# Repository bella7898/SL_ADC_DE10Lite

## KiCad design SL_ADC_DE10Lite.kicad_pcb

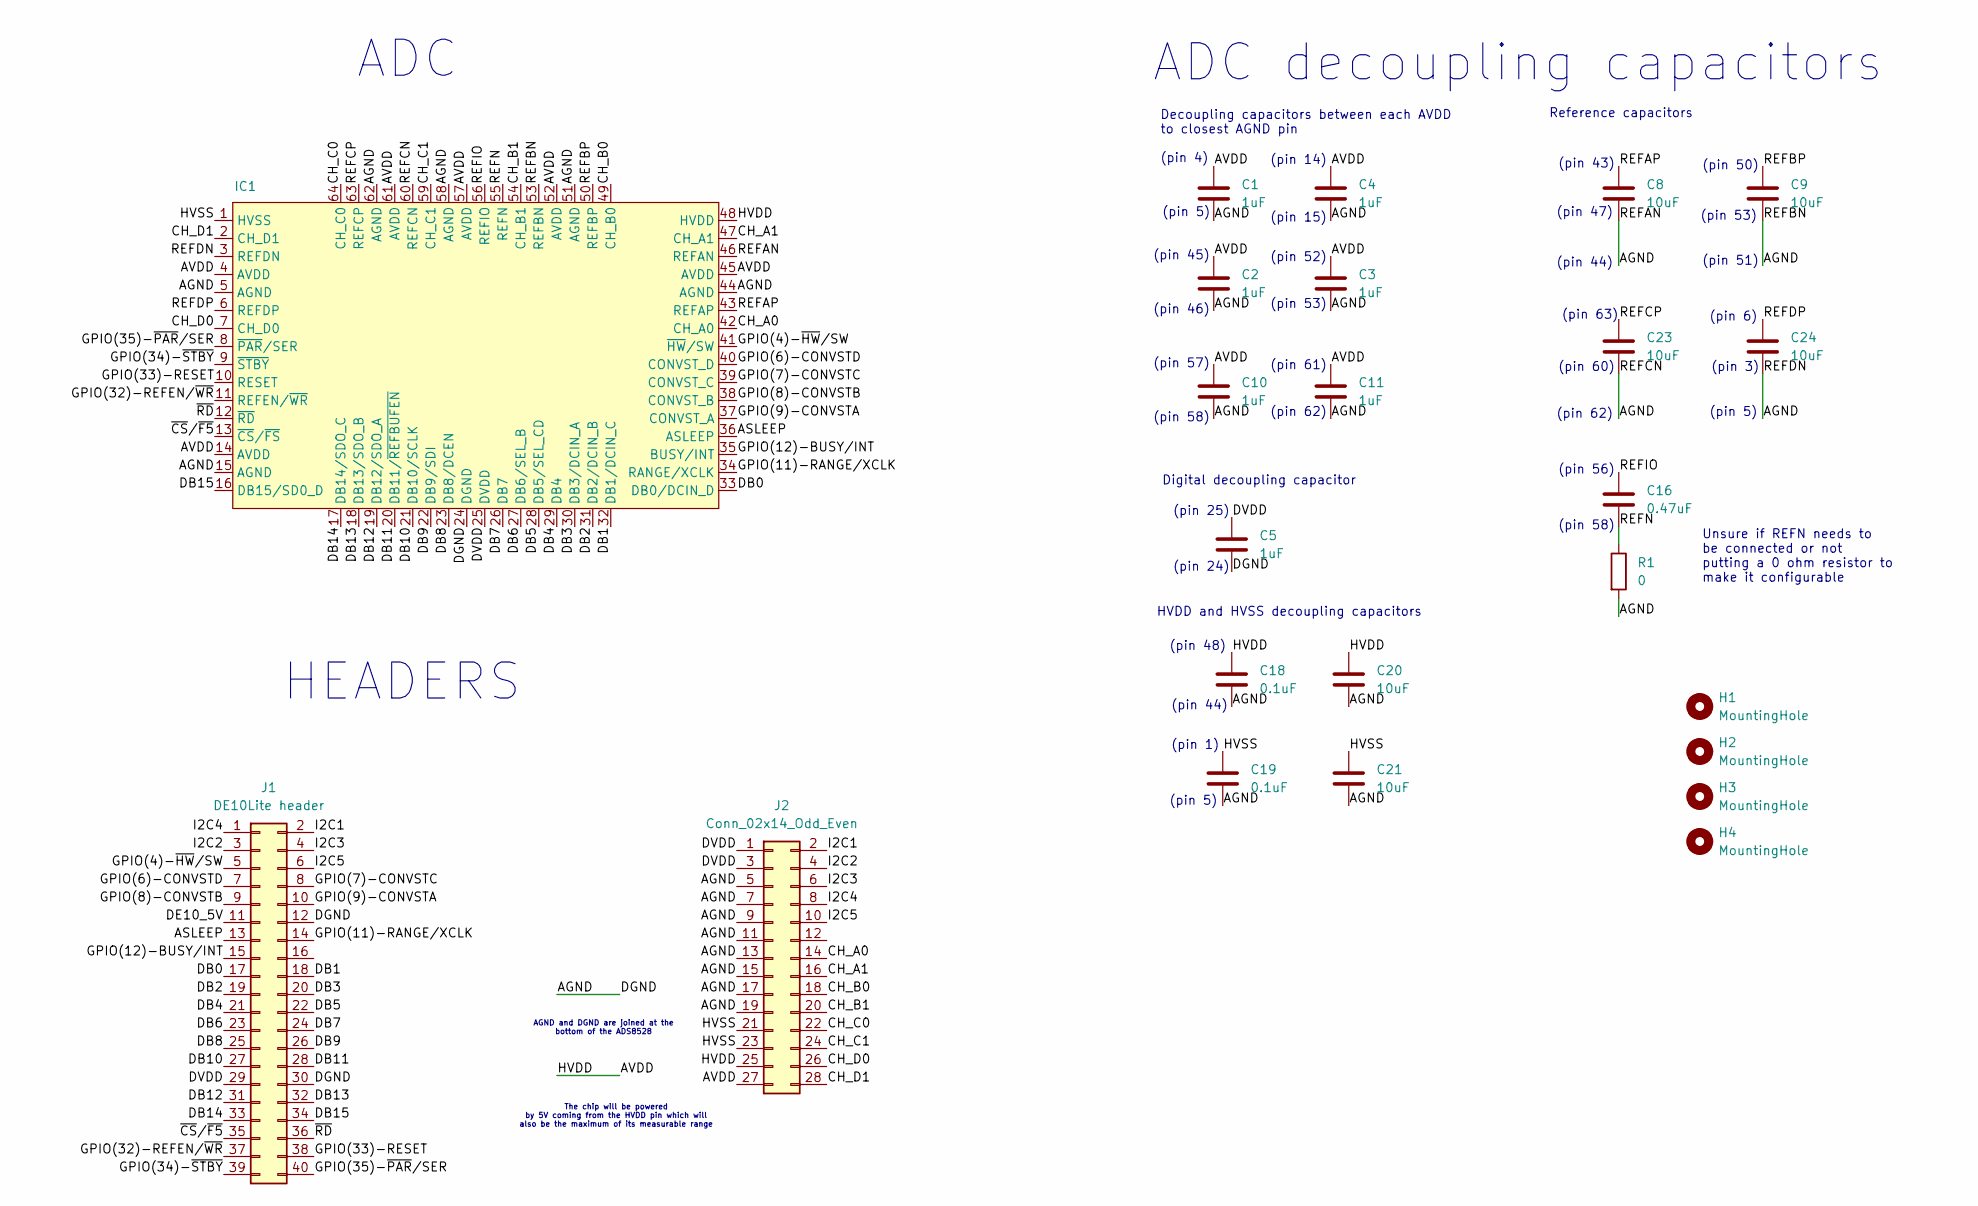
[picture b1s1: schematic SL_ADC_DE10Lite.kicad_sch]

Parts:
C1, C2, C3, C4, C5, C10, C11: 1uF; C_0805_2012Metric_Pad1.18x1.45mm_HandSolder; Manufacturer_Part_Number CL21B105KBFNNNE
C8, C9, C20, C21, C23, C24: 10uF; C_0805_2012Metric_Pad1.18x1.45mm_HandSolder; Manufacturer_Part_Number CL21B106KOQNNNE
C16: 0.47uF; C_0805_2012Metric_Pad1.18x1.45mm_HandSolder; Manufacturer_Part_Number CL21B106KOQNNNE
C18, C19: 0.1uF; C_0805_2012Metric_Pad1.18x1.45mm_HandSolder; Manufacturer_Part_Number CL21B106KOQNNNE
H1, H2, H3, H4: MountingHole; MountingHole_2.5mm
IC1: TQFP-64_10x10mm_P0.5mm
J1: DE10Lite header; PinHeader_2x20_P2.54mm_Vertical
J2: Conn_02x14_Odd_Even; PinHeader_2x14_P2.54mm_Vertical
R1: 0; LED_0805_2012Metric

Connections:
/AGND: C1.2, C2.2, C3.2, C4.2, C5.2, C8.2, C9.2, C10.2, C11.2, C18.2, C19.2, C20.2, C21.2, C23.2, C24.2, IC1.3 (REFDN), IC1.5 (AGND), IC1.15 (AGND), IC1.24 (DGND), IC1.44 (AGND), IC1.46 (REFAN), IC1.51 (AGND), IC1.53 (REFBN), IC1.58 (AGND), IC1.60 (REFCN), IC1.62 (AGND), J1.12, J1.30, J2.5, J2.7, J2.9, J2.11, J2.13, J2.15, J2.17, J2.19, R1.2
/ASLEEP: IC1.36 (ASLEEP), J1.13
/AVDD: C1.1, C2.1, C3.1, C4.1, C10.1, C11.1, C18.1, C20.1, IC1.4 (AVDD), IC1.14 (AVDD), IC1.45 (AVDD), IC1.48 (HVDD), IC1.52 (AVDD), IC1.57 (AVDD), IC1.61 (AVDD), J2.25, J2.27
/CH_A0: IC1.42 (CH_A0), J2.14
/CH_A1: IC1.47 (CH_A1), J2.16
/CH_B0: IC1.49 (CH_B0), J2.18
/CH_B1: IC1.54 (CH_B1), J2.20
/CH_C0: IC1.64 (CH_C0), J2.22
/CH_C1: IC1.59 (CH_C1), J2.24
/CH_D0: IC1.7 (CH_D0), J2.26
/CH_D1: IC1.2 (CH_D1), J2.28
/DB0: IC1.33 (DB0/DCIN_D), J1.17
/DB1: IC1.32 (DB1/DCIN_C), J1.18
/DB2: IC1.31 (DB2/DCIN_B), J1.19
/DB3: IC1.30 (DB3/DCIN_A), J1.20
/DB4: IC1.29 (DB4), J1.21
/DB5: IC1.28 (DB5/SEL_CD), J1.22
/DB6: IC1.27 (DB6/SEL_B), J1.23
/DB7: IC1.26 (DB7), J1.24
/DB8: IC1.23 (DB8/DCEN), J1.25
/DB9: IC1.22 (DB9/SDI), J1.26
/DB10: IC1.21 (DB10/SCLK), J1.27
/DB11: IC1.20 (DB11/~REFBUFEN), J1.28
/DB12: IC1.19 (DB12/SDO_A), J1.31
/DB13: IC1.18 (DB13/SDO_B), J1.32
/DB14: IC1.17 (DB14/SDO_C), J1.33
/DB15: IC1.16 (DB15/SD0_D), J1.34
/DE10_5V: J1.11
/DVDD: C5.1, IC1.25 (DVDD), J1.29, J2.1, J2.3
/GPIO(4)-~HW/SW: IC1.41 (~HW/SW), J1.5
/GPIO(6)-CONVSTD: IC1.40 (CONVST_D), J1.7
/GPIO(7)-CONVSTC: IC1.39 (CONVST_C), J1.8
/GPIO(8)-CONVSTB: IC1.38 (CONVST_B), J1.9
/GPIO(9)-CONVSTA: IC1.37 (CONVST_A), J1.10
/GPIO(11)-RANGE/XCLK: IC1.34 (RANGE/XCLK), J1.14
/GPIO(12)-BUSY/INT: IC1.35 (BUSY/INT), J1.15
/GPIO(32)-REFEN/~WR: IC1.11 (REFEN/~WR), J1.37
/GPIO(33)-RESET: IC1.10 (RESET), J1.38
/GPIO(34)-~STBY: IC1.9 (~STBY), J1.39
/GPIO(35)-~PAR/SER: IC1.8 (~PAR/SER), J1.40
/HVSS: C19.1, C21.1, IC1.1 (HVSS), J2.21, J2.23
/I2C1: J1.2, J2.2
/I2C2: J1.3, J2.4
/I2C3: J1.4, J2.6
/I2C4: J1.1, J2.8
/I2C5: J1.6, J2.10
/REFAP: C8.1, IC1.43 (REFAP)
/REFBP: C9.1, IC1.50 (REFBP)
/REFCP: C23.1, IC1.63 (REFCP)
/REFDP: C24.1, IC1.6 (REFDP)
/REFIO: C16.1, IC1.56 (REFIO)
/REFN: C16.2, IC1.55 (REFN), R1.1
/~CS/~F5: IC1.13 (~CS/~FS), J1.35
/~RD: IC1.12 (~RD), J1.36

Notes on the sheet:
(pin 14)
Digital decoupling capacitor
(pin 60)
AGND and DGND are joined at the bottom of the ADS8528
(pin 1)
HVDD and HVSS decoupling capacitors
(pin 4)
(pin 45)
ADC decoupling capacitors
Reference capacitors
(pin 62)
(pin 3)
(pin 15)
The chip will be powered by 5V coming from the HVDD pin which will also be the maximum of its measurable range
ADC
(pin 61)
(pin 50)
(pin 53)
(pin 47)
(pin 24)
Unsure if REFN needs to be connected or not putting a 0 ohm resistor to make it configurable
(pin 63)
(pin 43)
(pin 25)
(pin 51)
(pin 46)
(pin 57)
(pin 48)
(pin 5)
(pin 44)
(pin 58)
(pin 6)
Decoupling capacitors between each AVDD to closest AGND pin
(pin 56)
(pin 58)
(pin 52)
HEADERS

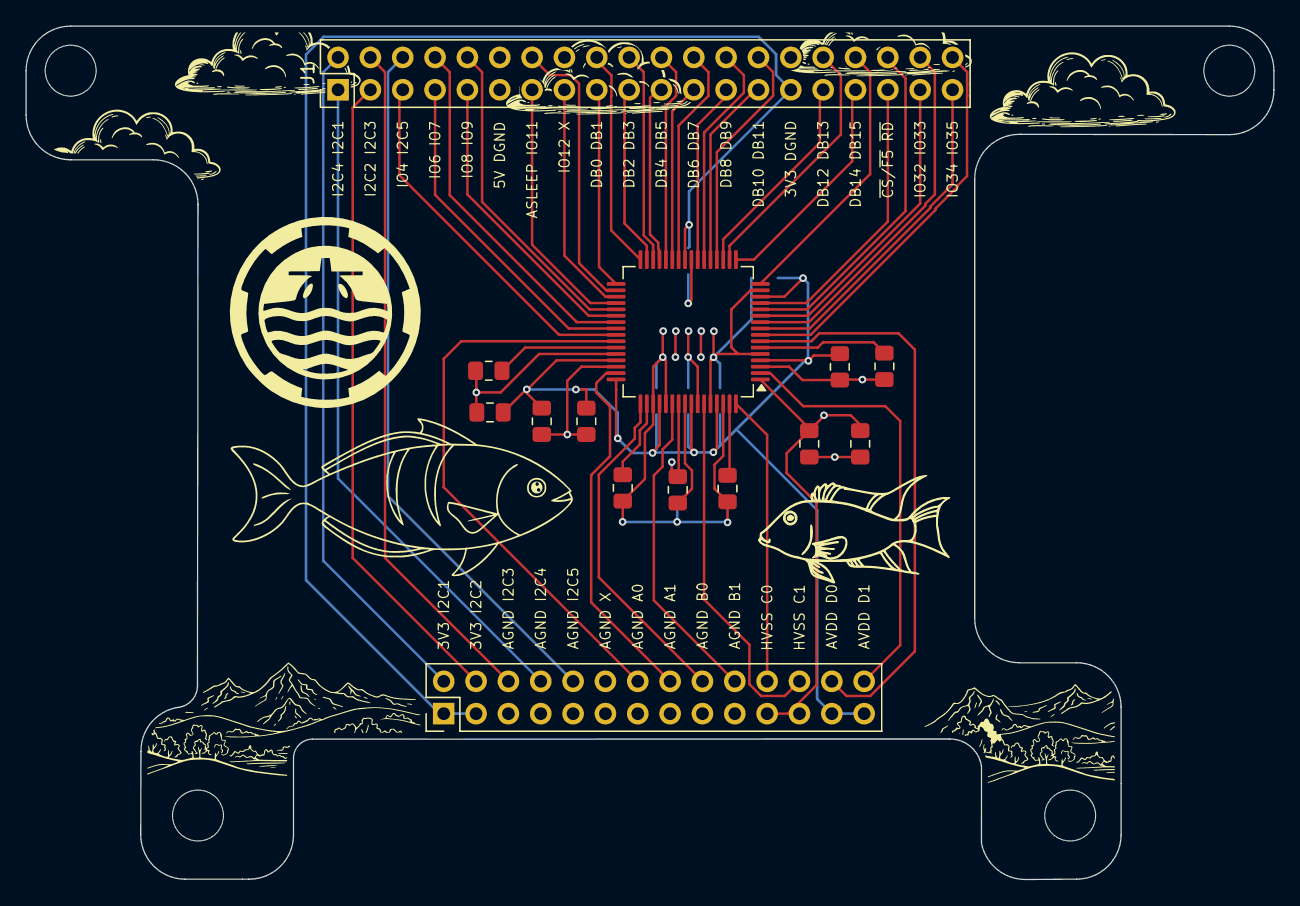
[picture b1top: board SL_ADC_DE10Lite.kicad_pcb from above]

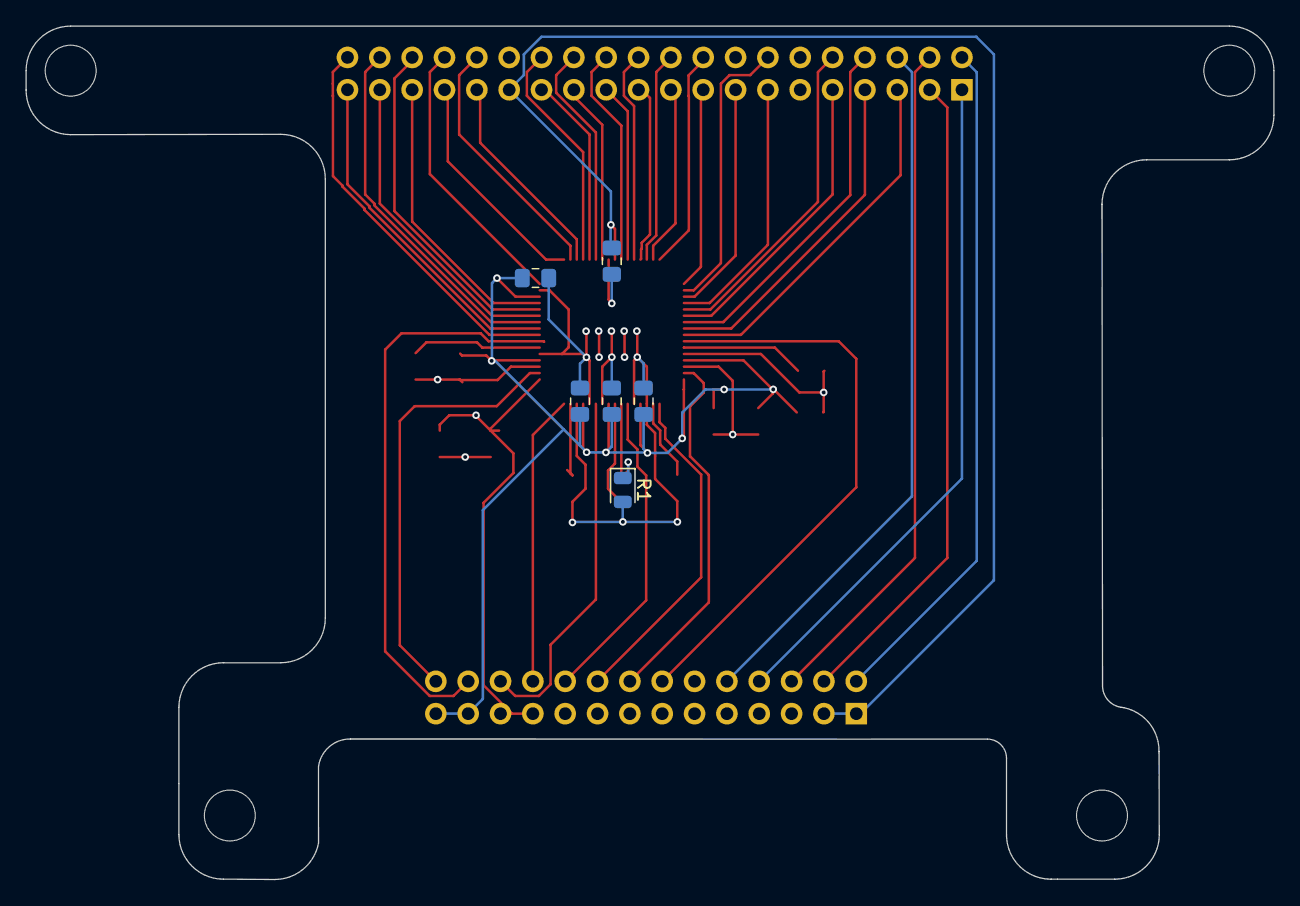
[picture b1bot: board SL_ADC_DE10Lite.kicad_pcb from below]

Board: 4 copper layers, 98.0 x 67.0 mm, 25 parts (6 on the bottom side), 53 nets.

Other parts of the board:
G: LOGO; SubbotsLogo

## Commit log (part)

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2026-05-15 Changes to decoupling capacitors
2026-05-30 Added inner copper layers and capacitor routes
2026-06-08 Update net names
2026-06-08 Add analog header
2026-06-12 left feedback for first run of work as comments and silkscreen labels. To be deleted
2026-06-13 some commments
2026-06-13 Revert "some commments"
    This reverts commit b9c0ff5e8d916fc042ee2d08fa9a5e41be4ebf5f.
2026-06-15 Add De10lite dimensions and routes
2026-06-15 Routing connections to DE10Lite header
2026-06-16 Define separate AGND and DGND copper fill
2026-06-27 Recent changes
2026-06-27 Updated version
2026-06-27 Rounded corners!!!
2026-06-27 Board outline error?
2026-06-28 Generated step file
